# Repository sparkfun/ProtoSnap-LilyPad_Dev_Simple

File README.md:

SparkFun ProtoSnap - LilyPad Development Simple
================================================

[*SparkFun ProtoSnap - LilyPad Development Simple (DEV-11201)*](https://www.sparkfun.com/products/11201)

The ProtoSnap LilyPad Simple Development board is a great way to get started in programmable e-textiles. 
By combining a LilyPad Simple board with 4 LED boards and a buzzer, the ProtoSnap LilyPad Simple Development board gives you everything you need to learn the basics. 

Repository Contents
-------------------

* **/Hardware** - All Eagle design files (.brd, .sch)

License Information
-------------------
The hardware is released under [Creative Commons ShareAlike 4.0 International](https://creativecommons.org/licenses/by-sa/4.0/).

Distributed as-is; no warranty is given.

_**Note:** A portion of this sale is given back to Dr. Leah Buechley for continued development and education of e-textiles and also to Arduino LLC to help fund continued development of new tools and new IDE features._

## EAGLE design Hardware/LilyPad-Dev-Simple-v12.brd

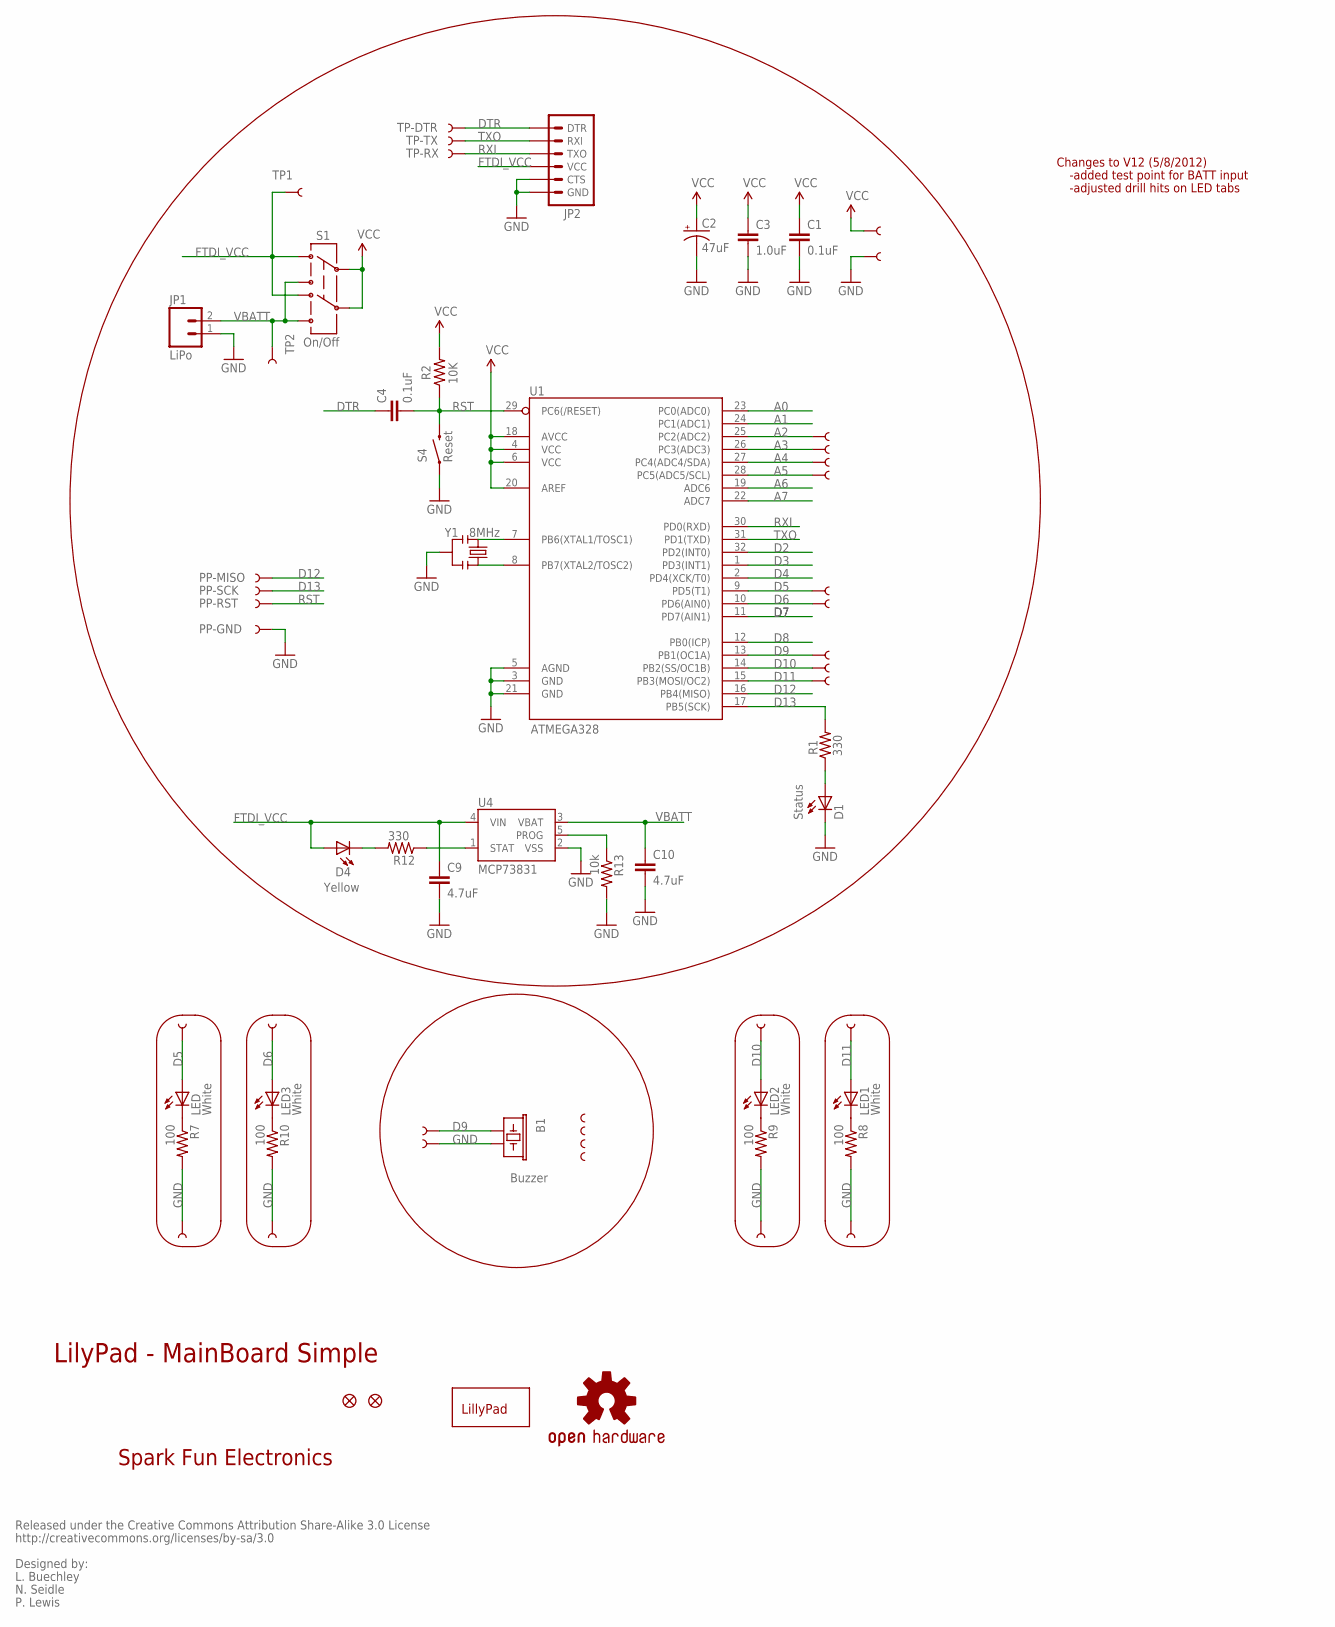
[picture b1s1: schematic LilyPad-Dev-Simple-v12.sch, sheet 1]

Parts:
1, 2, 3, 4: SEWTAP-NOHOLE2; PETAL-NOHOLE-2SIDE
A2/16, A3/17, A4/18, A5/19: SEWTAP9; PETAL-LONG-1-2SIDE
B1: Buzzer; BUZZER-CCV
C1, C4: 0.1uF; 0402-CAP
C2: 47uF; EIA3528
C3: 1.0uF; 0402-CAP
C9, C10: 4.7uF; 0402-CAP
D1: Status; LED-0603
D4: Yellow; LED-0603
JP1: LiPo; JST-2-SMD
JP2: ARDUINO_SERIAL_PROGRAMSMD; 1X06-SMD
JP3, JP4: FIDUCIAL1X2; FIDUCIAL-1X2
LED, LED1, LED2, LED3: White; LED-1206
LED+, LED+1, LED+2, LED+3: SEWTAP6; PETAL-SMALL-2SIDE
LED-, LED-1, LED-2, LED-3: SEWTAP6; PETAL-SMALL-2SIDE
LOGO: LOGO-LPLPA; LOGO-LPA
PP-GND: TEST-POINT3X5; PAD.03X.05
PP-MISO: TEST-POINT3X5; PAD.03X.05
PP-RST: TEST-POINT3X5; PAD.03X.05
PP-SCK: TEST-POINT3X5; PAD.03X.05
R1, R12: 330; 0402-RES
R2: 10K; 0402-RES
R7, R8, R9, R10: 100; 0603-RES
R13: 10k; 0402-RES
S1: On/Off; AYZ0202
S4: Reset; TACTILE_SWITCH_SMD
TP1, TP2: TEST-POINT3X5; PAD.03X.05
TP-DTR: TEST-POINT3X5; PAD.03X.05
TP-RX: TEST-POINT3X5; PAD.03X.05
TP-TX: TEST-POINT3X5; PAD.03X.05
U1: ATMEGA328; TQFP32-08
U4: MCP73831; SOT23-5
U$1, U$4, U$37, U$39, U$41, U$43, U$45: SEWTAP9; PETAL-LONG-1-2SIDE
U$2: OSHW-LOGOS; OSHW-LOGO-S
U$32-, U$33+: SEWTAP6; PETAL-SMALL
Y1: 8MHz; RESONATOR-SMD

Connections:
A0: U1.23 (PC0(ADC0))
A1: U1.24 (PC1(ADC1))
A2: A2/16.1, U1.25 (PC2(ADC2))
A3: A3/17.1, U1.26 (PC3(ADC3))
A4: A4/18.1, U1.27 (PC4(ADC4/SDA))
A5: A5/19.1, U1.28 (PC5(ADC5/SCL))
A6: U1.19 (ADC6)
A7: U1.22 (ADC7)
D2: U1.32 (PD2(INT0))
D3: U1.1 (PD3(INT1))
D4: U1.2 (PD4(XCK/T0))
D5: LED.A, LED+.1, U1.9 (PD5(T1)), U$41.1
D6: LED3.A, LED+3.1, U1.10 (PD6(AIN0)), U$1.1
D7: U1.11 (PD7(AIN1))
D8: U1.12 (PB0(ICP))
D9: B1.+ (1), U1.13 (PB1(OC1A)), U$33+.1, U$37.1
D10: LED2.A, LED+2.1, U1.14 (PB2(SS/OC1B)), U$39.1
D11: LED1.A, LED+1.1, U1.15 (PB3(MOSI/OC2)), U$4.1
D12: PP-MISO.P$1, U1.16 (PB4(MISO))
D13: PP-SCK.P$1, R1.2, U1.17 (PB5(SCK))
DTR: C4.1, JP2.1 (DTR), TP-DTR.P$1
FTDI_VCC: C9.1, D4.A, JP2.4 (VCC), S1.3 (1), S1.6 (4), TP1.P$1, U4.4 (VIN)
GND: B1.- (2), C1.2, C2.C (-), C3.2, C9.2, C10.2, D1.C, JP1.1, JP2.5 (CTS), JP2.6 (GND), LED-.1, LED-1.1, LED-2.1, LED-3.1, PP-GND.P$1, R7.2, R8.2, R9.2, R10.2, R13.2, S4.1, U1.3 (GND), U1.5 (AGND), U1.21 (GND), U4.2 (VSS), U$32-.1, U$43.1, Y1.2
unnamed: U1.7 (PB6(XTAL1/TOSC1)), Y1.1
unnamed: D1.A, R1.1
unnamed: U1.8 (PB7(XTAL2/TOSC2)), Y1.3
unnamed: LED.C, R7.1
unnamed: LED1.C, R8.1
unnamed: LED2.C, R9.1
unnamed: LED3.C, R10.1
unnamed: D4.C, R12.2
PROG: R13.1, U4.5 (PROG)
RST: C4.2, PP-RST.P$1, R2.1, S4.3 (2), U1.29 (PC6(/RESET))
RXI: JP2.3 (TXO), TP-RX.P$1, U1.30 (PD0(RXD))
STAT: R12.1, U4.1 (STAT)
TXO: JP2.2 (RXI), TP-TX.P$1, U1.31 (PD1(TXD))
VBATT: C10.1, JP1.2, S1.1 (3), S1.4 (6), TP2.P$1, U4.3 (VBAT)
VCC: C1.1, C2.A (+), C3.1, R2.2, S1.2, S1.5, U1.4 (VCC), U1.6 (VCC), U1.18 (AVCC), U1.20 (AREF), U$45.1

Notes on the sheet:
LilyPad - MainBoard Simple
Spark Fun Electronics
Released under the Creative Commons Attribution Share-Alike 3.0 License
http://creativecommons.org/licenses/by-sa/3.0
Designed by:
L. Buechley
N. Seidle
P. Lewis
Changes to V12 (5/8/2012)
-added test point for BATT input
-adjusted drill hits on LED tabs

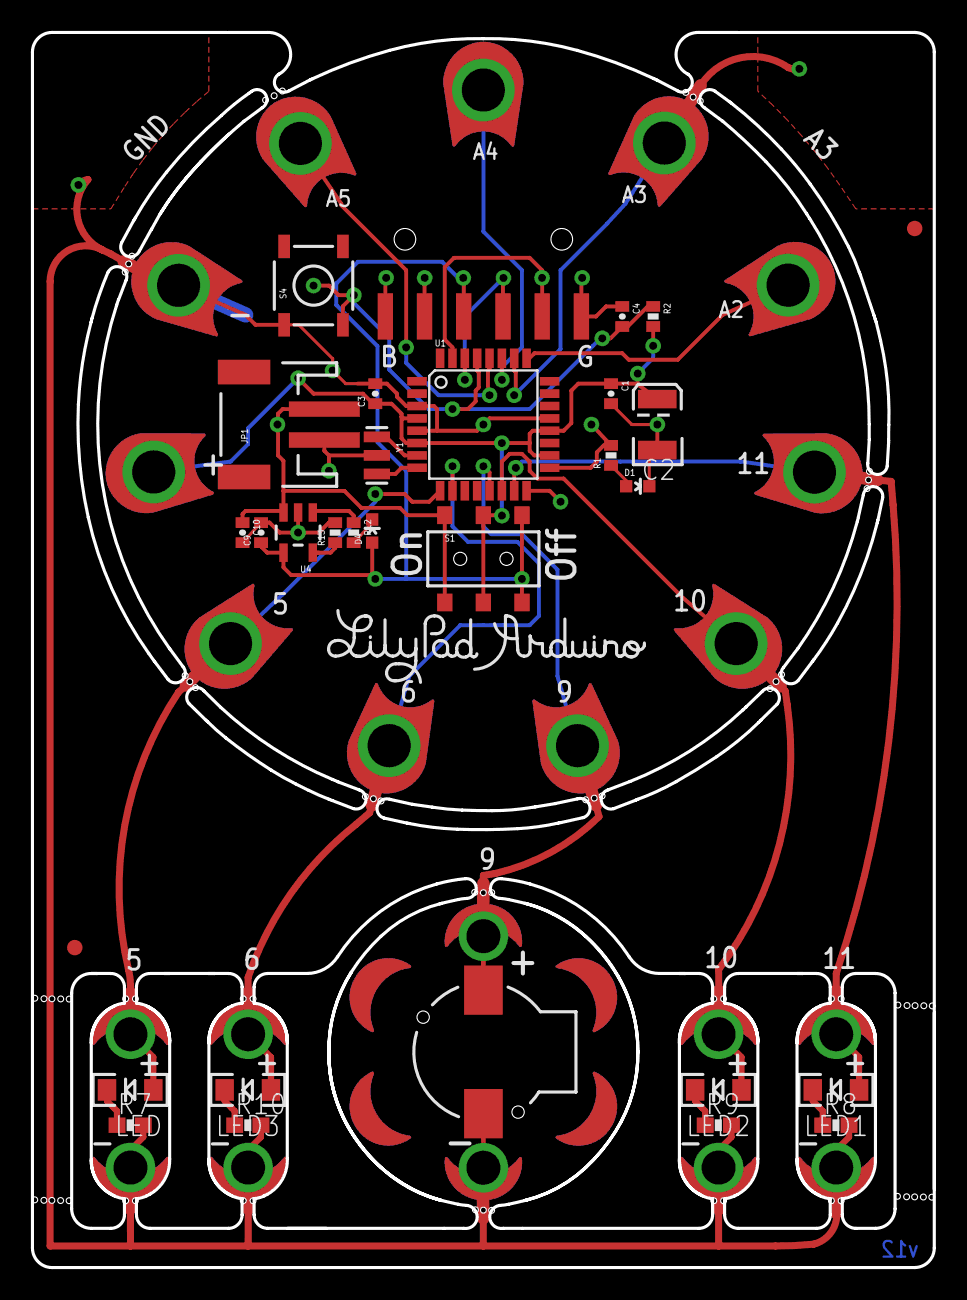
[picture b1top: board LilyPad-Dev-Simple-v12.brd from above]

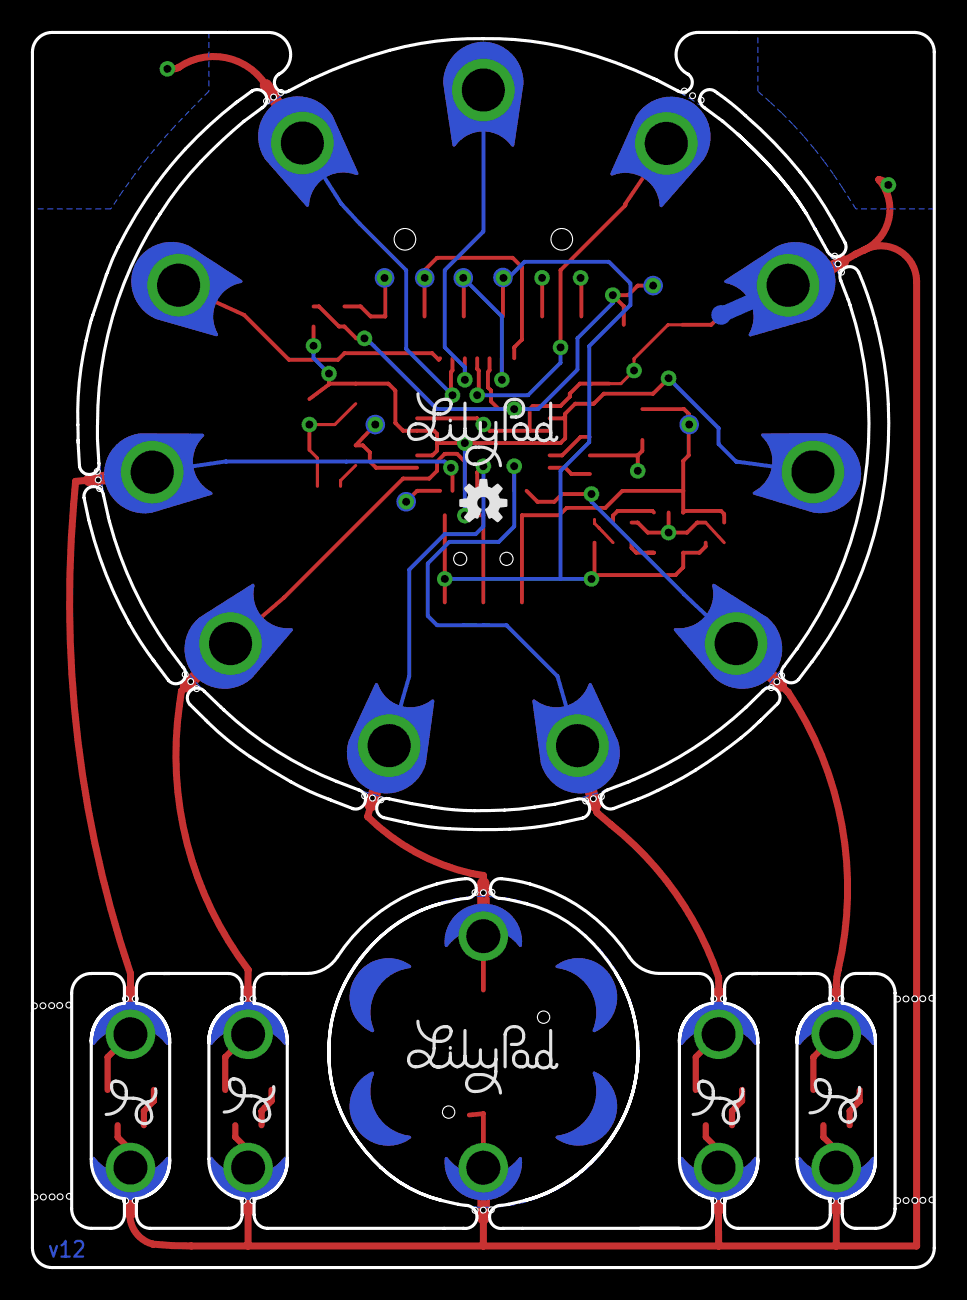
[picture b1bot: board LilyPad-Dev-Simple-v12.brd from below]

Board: 2 copper layers, 58.4 x 80.0 mm, 73 parts (16 on the bottom side), 29 nets.

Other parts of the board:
LOGO3, LOGO4, LOGO5, LOGO6: LOGO-LPL; LOGO-L
U$21, U$35: LOGO-LPLP; LOGO-LILYPAD
U$36: LILYPAD-BRD-LAYERS-SMALL

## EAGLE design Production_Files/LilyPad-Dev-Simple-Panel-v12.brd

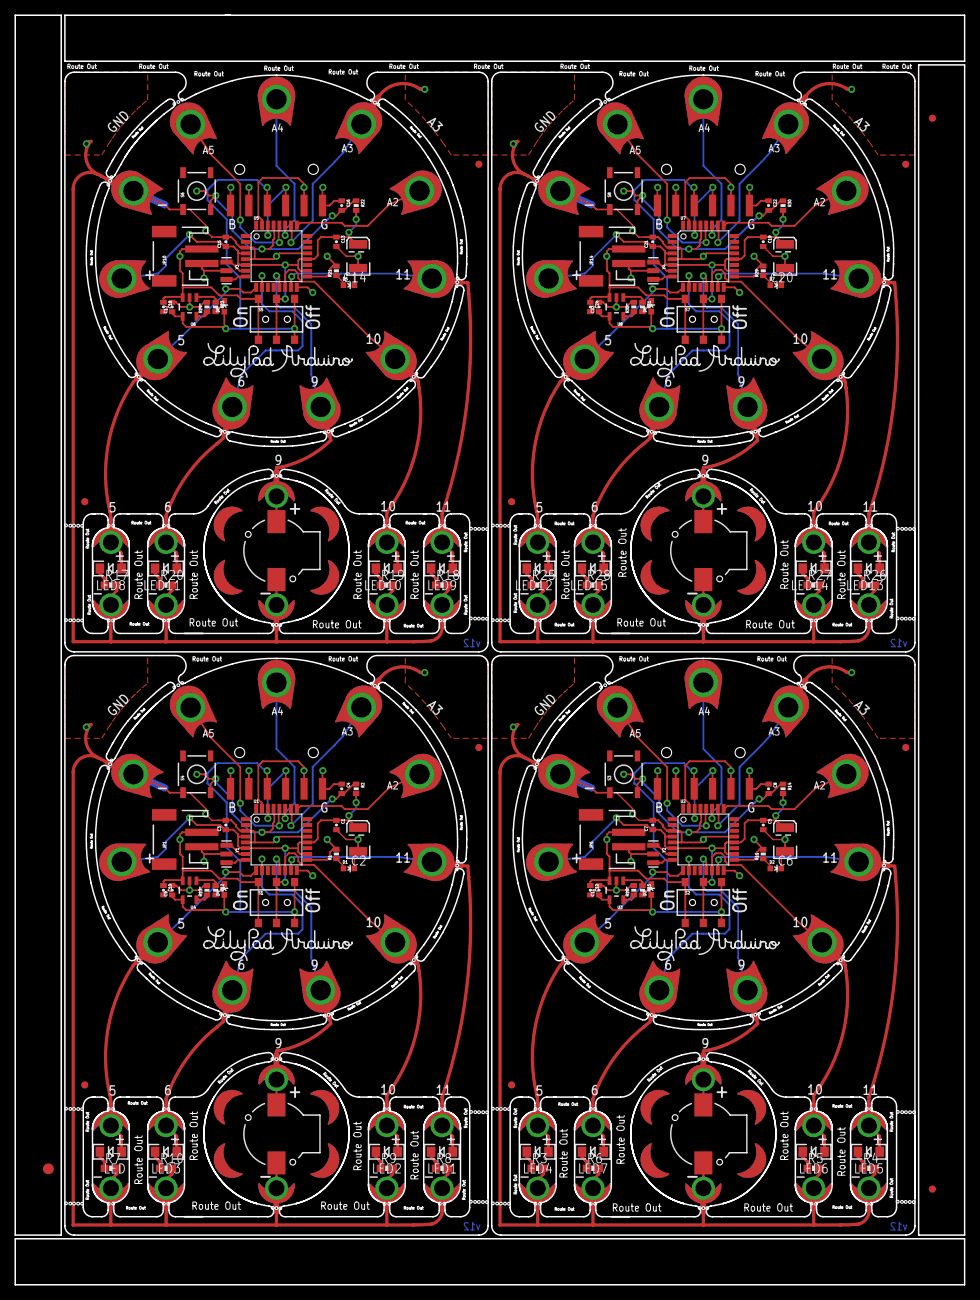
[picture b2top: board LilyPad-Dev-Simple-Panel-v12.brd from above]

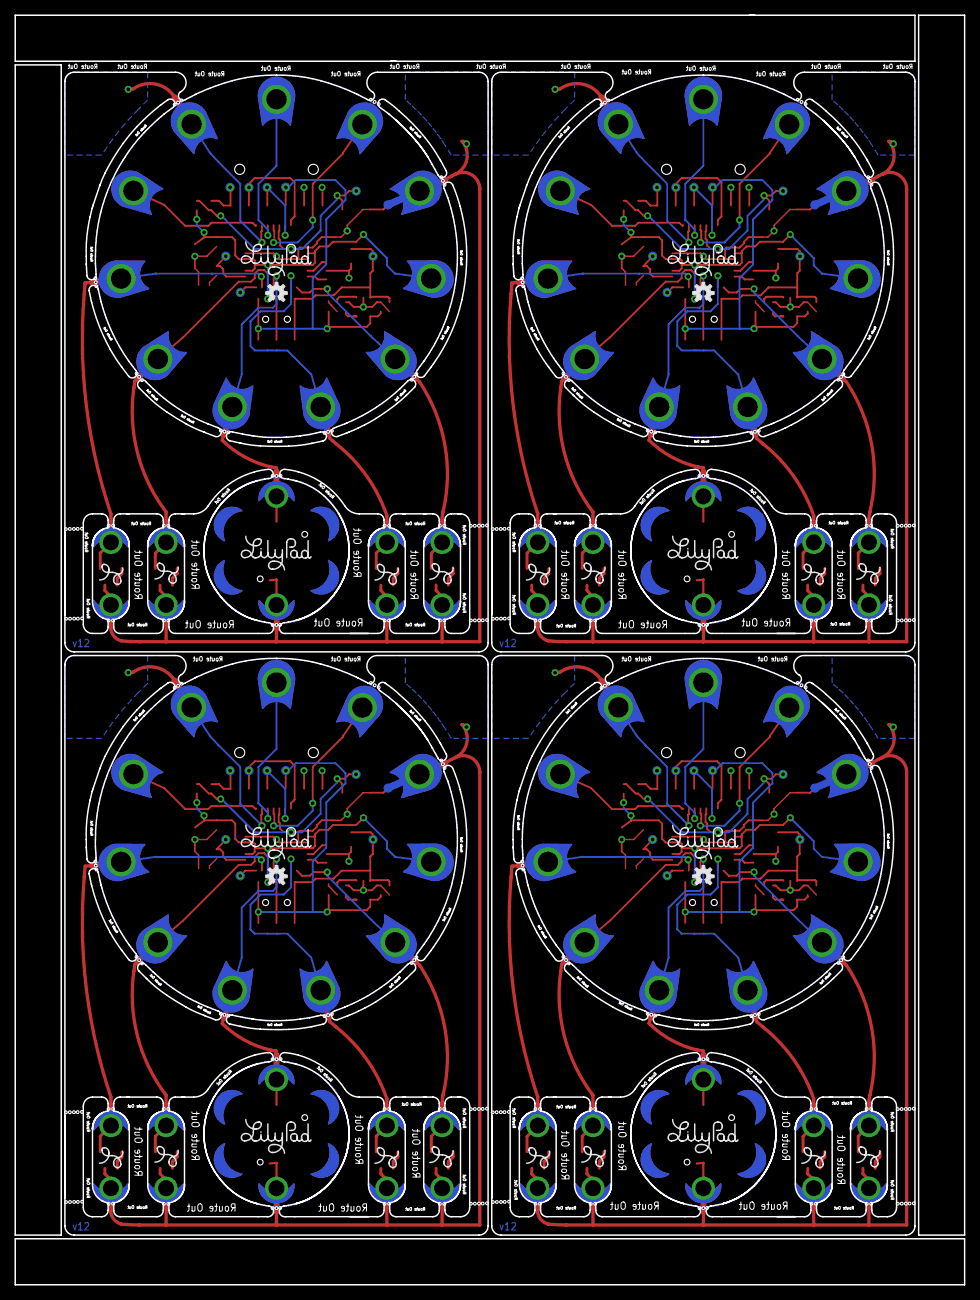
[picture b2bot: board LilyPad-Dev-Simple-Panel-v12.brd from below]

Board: 2 copper layers, 131.1 x 175.3 mm, 295 parts (64 on the bottom side), 116 nets.

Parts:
1, 2, 3, 4, 5, 6, 7, 8, 9, 10, 11, 12, 13, 14, 15, 16: SEWTAP-NOHOLE2; PETAL-NOHOLE-2SIDE
A2/1, A2/2, A2/3, A2/16, A3/1, A3/2, A3/3, A3/17, A4/1, A4/2, A4/3, A4/18, A5/1, A5/2, A5/3, A5/19: SEWTAP9; PETAL-LONG-1-2SIDE
B1, B2, B3, B4: Buzzer; BUZZER-CCV
C1, C4, C5, C8, C13, C16, C19, C22: 0.1uF; 0402-CAP
C2, C6, C14, C20: 47uF; EIA3528
C3, C7, C15, C21: 1.0uF; 0402-CAP
C9, C10, C11, C12, C17, C18, C23, C24: 4.7uF; 0402-CAP
D1, D2, D5, D7: Status; LED-0603
D3, D4, D6, D8: Yellow; LED-0603
E$1: FIDUCIAL-1.5X3
E$4, E$5: FIDUCIAL-1X2
JP1, JP6, JP10, JP14: LiPo; JST-2-SMD
JP2, JP5, JP9, JP13: 1X06-SMD
JP3, JP4, JP7, JP8, JP11, JP12, JP15, JP16: FIDUCIAL1X2; FIDUCIAL-1X2
LED, LED1, LED2, LED3, LED4, LED5, LED6, LED7, LED8, LED9, LED10, LED11, LED12, LED13, LED14, LED15: White; LED-1206
LED+, LED+1, LED+2, LED+3, LED+4, LED+5, LED+6, LED+7, LED+8, LED+9, LED+10, LED+11, LED+12, LED+13, LED+14, LED+15: SEWTAP6; PETAL-SMALL-2SIDE
LED-, LED-1, LED-2, LED-3, LED-4, LED-5, LED-6, LED-7, LED-8, LED-9, LED-10, LED-11, LED-12, LED-13, LED-14, LED-15: SEWTAP6; PETAL-SMALL-2SIDE
LOGO, LOGO9, LOGO14, LOGO19: LOGO-LPLPA; LOGO-LPA
LOGO1, LOGO2, LOGO3, LOGO4, LOGO5, LOGO6, LOGO7, LOGO8, LOGO10, LOGO11, LOGO12, LOGO13, LOGO15, LOGO16, LOGO17, LOGO18: LOGO-LPL; LOGO-L
PP-GND, PP-GND1, PP-GND2, PP-GND3: PAD.03X.05
PP-MISO, PP-MISO1, PP-MISO2, PP-MISO3: PAD.03X.05
PP-RST, PP-RST1, PP-RST2, PP-RST3: PAD.03X.05
PP-SCK, PP-SCK1, PP-SCK2, PP-SCK3: PAD.03X.05
R1, R11, R12, R15, R21, R23, R29, R31: 330; 0402-RES
R2, R14, R22, R30: 10K; 0402-RES
R3, R4, R5, R6, R7, R8, R9, R10, R17, R18, R19, R20, R25, R26, R27, R28: 100; 0603-RES
R13, R16, R24, R32: 10k; 0402-RES
S1, S2, S5, S7: On/Off; AYZ0202
S3, S4, S6, S8: Reset; TACTILE_SWITCH_SMD
TP1, TP2, TP3, TP4, TP5, TP6, TP7, TP8: PAD.03X.05
TP-DTR, TP-DTR1, TP-DTR2, TP-DTR3: PAD.03X.05
TP-RX, TP-RX1, TP-RX2, TP-RX3: PAD.03X.05
TP-TX, TP-TX1, TP-TX2, TP-TX3: PAD.03X.05
U1, U2, U5, U7: ATMEGA328; TQFP32-08
U3, U4, U6, U8: MCP73831; SOT23-5
U$1, U$4, U$5, U$6, U$7, U$8, U$9, U$10, U$11, U$16, U$17, U$18, U$19, U$20, U$22, U$23, U$28, U$29, U$30, U$31, U$32, U$33, U$34, U$37, U$39, U$41, U$43, U$45: SEWTAP9; PETAL-LONG-1-2SIDE
U$2, U$14, U$26, U$42: OSHW-LOGOS; OSHW-LOGO-S
U$3, U$12, U$15, U$21, U$24, U$27, U$35, U$38: LOGO-LPLP; LOGO-LILYPAD
U$13, U$25, U$36, U$40: LILYPAD-BRD-LAYERS-SMALL
U$32-, U$32-1, U$32-2, U$32-3, U$33+, U$33+1, U$33+2, U$33+3: SEWTAP6; PETAL-SMALL-2SIDE
Y1, Y2, Y3, Y4: 8MHz; RESONATOR-SMD

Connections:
A2: A2/16.1, U1.25
A3: A3/17.1, U1.26
A4: A4/18.1, U1.27
A5: A5/19.1, U1.28
A8: A2/1.1, U2.25
A9: A3/1.1, U2.26
A10: A4/1.1, U2.27
A11: A5/1.1, U2.28
A16: A2/2.1, U5.25
A17: A3/2.1, U5.26
A18: A4/2.1, U5.27
A19: A5/2.1, U5.28
A24: A2/3.1, U7.25
A25: A3/3.1, U7.26
A26: A4/3.1, U7.27
A27: A5/3.1, U7.28
D1: LED5.A, LED+5.1, U2.15, U$11.1
D5: LED.A, LED+.1, U1.9, U$41.1
D6: LED3.A, LED+3.1, U1.10, U$1.1
D9: B1.+, U1.13, U$33+.1, U$37.1
D10: LED2.A, LED+2.1, U1.14, U$39.1
D11: LED1.A, LED+1.1, U1.15, U$4.1
D12: PP-MISO.P$1, U1.16
D13: PP-SCK.P$1, R1.2, U1.17
D14: PP-SCK1.P$1, R11.2, U2.17
D15: LED4.A, LED+4.1, U2.9, U$8.1
D16: B2.+, U2.13, U$6.1, U$33+1.1
D17: LED7.A, LED+7.1, U2.10, U$5.1
D18: LED6.A, LED+6.1, U2.14, U$7.1
D24: PP-MISO1.P$1, U2.16
D25: LED9.A, LED+9.1, U5.15, U$23.1
D26: PP-SCK2.P$1, R21.2, U5.17
D27: LED8.A, LED+8.1, U5.9, U$19.1
D28: B3.+, U5.13, U$17.1, U$33+2.1
D29: LED11.A, LED+11.1, U5.10, U$16.1
D30: LED10.A, LED+10.1, U5.14, U$18.1
D36: PP-MISO2.P$1, U5.16
D37: LED13.A, LED+13.1, U7.15, U$34.1
D38: PP-SCK3.P$1, R29.2, U7.17
D39: LED12.A, LED+12.1, U7.9, U$31.1
D40: B4.+, U7.13, U$29.1, U$33+3.1
D41: LED15.A, LED+15.1, U7.10, U$28.1
D42: LED14.A, LED+14.1, U7.14, U$30.1
D48: PP-MISO3.P$1, U7.16
DTR: C4.1, JP2.1, TP-DTR.P$1
DTR1: C8.1, JP5.1, TP-DTR1.P$1
DTR2: C16.1, JP9.1, TP-DTR2.P$1
DTR3: C22.1, JP13.1, TP-DTR3.P$1
FTDI_VCC: C9.1, D4.A, JP2.4, S1.3, S1.6, TP1.P$1, U4.4
FTDI_VCC1: C11.1, D3.A, JP5.4, S2.3, S2.6, TP3.P$1, U3.4
FTDI_VCC2: C17.1, D6.A, JP9.4, S5.3, S5.6, TP5.P$1, U6.4
FTDI_VCC3: C23.1, D8.A, JP13.4, S7.3, S7.6, TP7.P$1, U8.4
GND: B1.-, C1.2, C2.C, C3.2, C9.2, C10.2, D1.C, JP1.1, JP2.5, JP2.6, LED-.1, LED-1.1, LED-2.1, LED-3.1, PP-GND.P$1, R7.2, R8.2, R9.2, R10.2, R13.2, S4.1, U1.3, U1.5, U1.21, U4.2, U$32-.1, U$43.1, Y1.2
GND1: B2.-, C5.2, C6.C, C7.2, C11.2, C12.2, D2.C, JP5.5, JP5.6, JP6.1, LED-4.1, LED-5.1, LED-6.1, LED-7.1, PP-GND1.P$1, R3.2, R4.2, R5.2, R6.2, R16.2, S3.1, U2.3, U2.5, U2.21, U3.2, U$9.1, U$32-1.1, Y2.2
GND2: B3.-, C13.2, C14.C, C15.2, C17.2, C18.2, D5.C, JP9.5, JP9.6, JP10.1, LED-8.1, LED-9.1, LED-10.1, LED-11.1, PP-GND2.P$1, R17.2, R18.2, R19.2, R20.2, R24.2, S6.1, U5.3, U5.5, U5.21, U6.2, U$20.1, U$32-2.1, Y3.2
GND3: B4.-, C19.2, C20.C, C21.2, C23.2, C24.2, D7.C, JP13.5, JP13.6, JP14.1, LED-12.1, LED-13.1, LED-14.1, LED-15.1, PP-GND3.P$1, R25.2, R26.2, R27.2, R28.2, R32.2, S8.1, U7.3, U7.5, U7.21, U8.2, U$32.1, U$32-3.1, Y4.2
unnamed: U1.7, Y1.1
unnamed: D1.A, R1.1
unnamed: U1.8, Y1.3
unnamed: LED4.C, R3.1
unnamed: LED5.C, R4.1
unnamed: LED6.C, R5.1
unnamed: LED7.C, R6.1
unnamed: D2.A, R11.1
unnamed: U2.7, Y2.1
unnamed: U2.8, Y2.3
unnamed: D3.C, R15.2
unnamed: LED8.C, R17.1
unnamed: LED9.C, R18.1
unnamed: LED10.C, R19.1
unnamed: LED11.C, R20.1
unnamed: LED.C, R7.1
unnamed: D5.A, R21.1
unnamed: U5.7, Y3.1
unnamed: LED1.C, R8.1
unnamed: U5.8, Y3.3
unnamed: D6.C, R23.2
unnamed: LED2.C, R9.1
unnamed: LED12.C, R25.1
unnamed: LED3.C, R10.1
unnamed: LED13.C, R26.1
unnamed: LED14.C, R27.1
unnamed: LED15.C, R28.1
unnamed: D7.A, R29.1
unnamed: U7.7, Y4.1
unnamed: D4.C, R12.2
unnamed: U7.8, Y4.3
unnamed: D8.C, R31.2
PROG: R13.1, U4.5
PROG1: R16.1, U3.5
PROG2: R24.1, U6.5
PROG3: R32.1, U8.5
RST: C4.2, PP-RST.P$1, R2.1, S4.3, U1.29
RST1: C8.2, PP-RST1.P$1, R14.1, S3.3, U2.29
RST2: C16.2, PP-RST2.P$1, R22.1, S6.3, U5.29
RST3: C22.2, PP-RST3.P$1, R30.1, S8.3, U7.29
RXI: JP2.3, TP-RX.P$1, U1.30
RXI1: JP5.3, TP-RX1.P$1, U2.30
RXI2: JP9.3, TP-RX2.P$1, U5.30
RXI3: JP13.3, TP-RX3.P$1, U7.30
STAT: R12.1, U4.1
STAT1: R15.1, U3.1
STAT2: R23.1, U6.1
STAT3: R31.1, U8.1
TXO: JP2.2, TP-TX.P$1, U1.31
TXO1: JP5.2, TP-TX1.P$1, U2.31
TXO2: JP9.2, TP-TX2.P$1, U5.31
TXO3: JP13.2, TP-TX3.P$1, U7.31
VBATT: C10.1, JP1.2, S1.1, S1.4, TP2.P$1, U4.3
VBATT1: C12.1, JP6.2, S2.1, S2.4, TP4.P$1, U3.3
VBATT2: C18.1, JP10.2, S5.1, S5.4, TP6.P$1, U6.3
VBATT3: C24.1, JP14.2, S7.1, S7.4, TP8.P$1, U8.3
VCC: C1.1, C2.A, C3.1, R2.2, S1.2, S1.5, U1.4, U1.6, U1.18, U1.20, U$45.1
VCC1: C5.1, C6.A, C7.1, R14.2, S2.2, S2.5, U2.4, U2.6, U2.18, U2.20, U$10.1
VCC2: C13.1, C14.A, C15.1, R22.2, S5.2, S5.5, U5.4, U5.6, U5.18, U5.20, U$22.1
VCC3: C19.1, C20.A, C21.1, R30.2, S7.2, S7.5, U7.4, U7.6, U7.18, U7.20, U$33.1

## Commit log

2015-03-10 Adding hardware files, updating README
2015-05-26 created panel v12

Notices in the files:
parts and their libraries:
SparkFun-Aesthetics: Licensing: CC v3.0 Share-Alike You are welcome to use this library for commercial purposes.
SparkFun-Retired: Licensing:Creative Commons ShareAlike 4.0 International - https://creativecommons.org/licenses/by-sa/4.0
